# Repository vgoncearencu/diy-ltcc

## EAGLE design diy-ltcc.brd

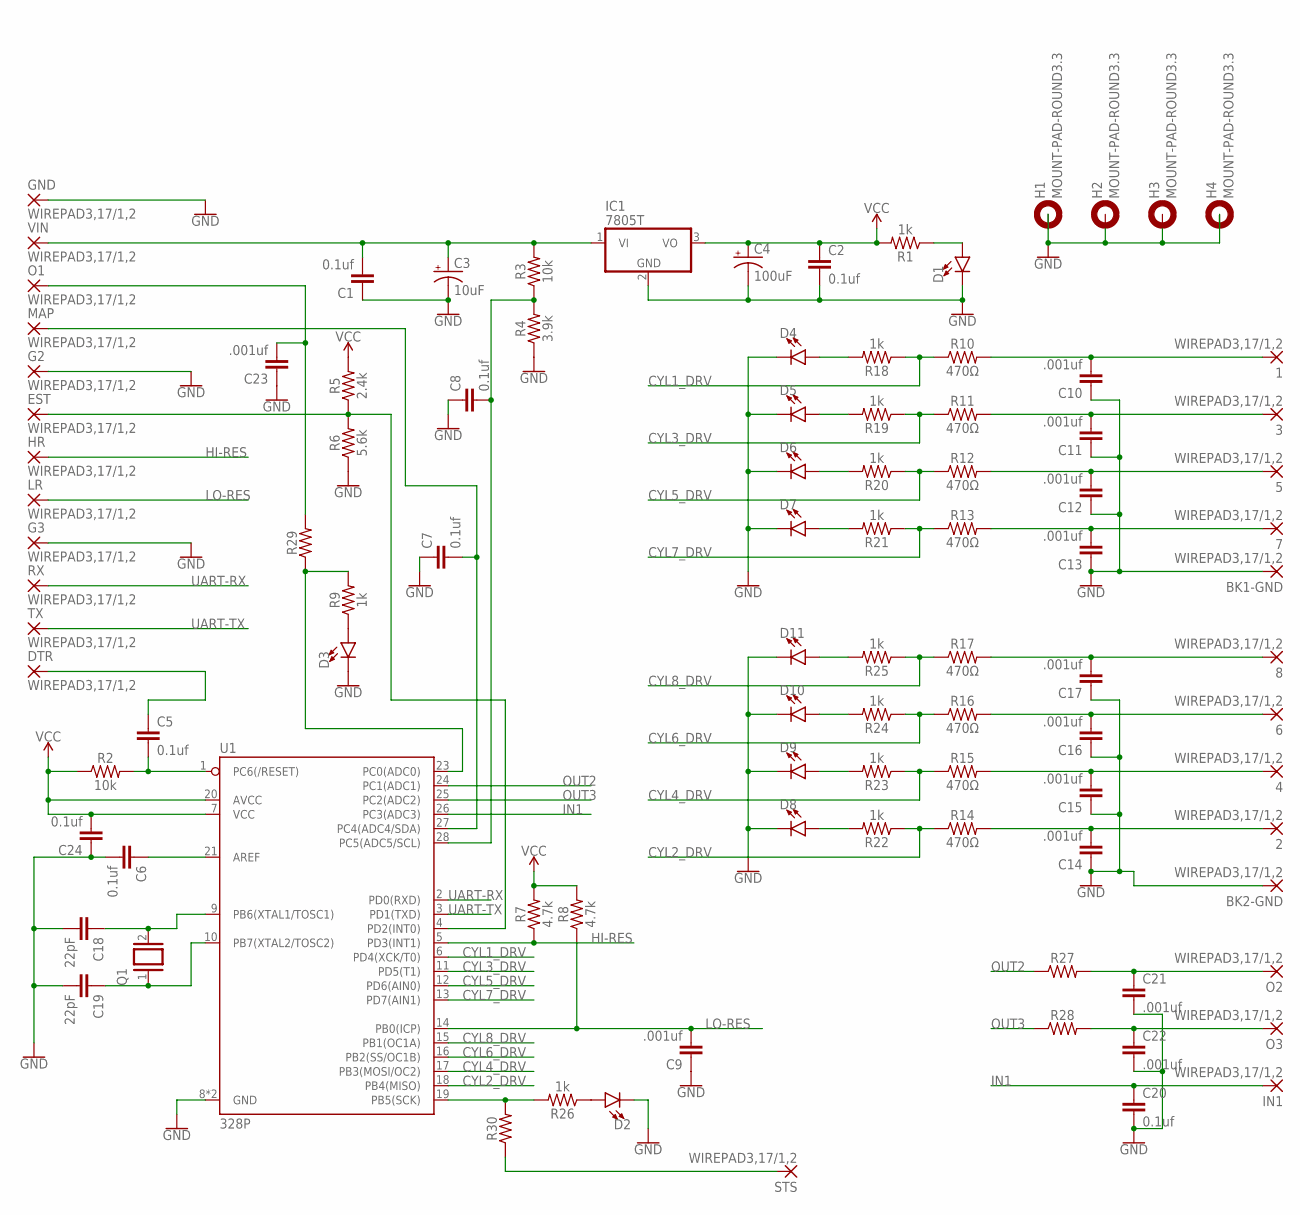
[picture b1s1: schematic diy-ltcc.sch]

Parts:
1, 2, 3, 4, 5, 6, 7, 8: WIREPAD3,17/1,2; 3,17/1,2
BK1-GND, BK2-GND: WIREPAD3,17/1,2; 3,17/1,2
C1, C2, C5, C6, C7, C8, C20, C24: 0.1uf; CAP-PTH-2.54
C3: 10uF; CPOL-RADIAL-2.5MM-5MM-KIT
C4: 100uF; CPOL-RADIAL-2.5MM-6.5MM
C9, C10, C11, C12, C13, C14, C15, C16, C17, C21, C22, C23: .001uf; CAP-PTH-2.54
C18, C19: 22pF; CAP-PTH-2.54
D1, D2, D3, D4, D5, D6, D7, D8, D9, D10, D11: LED3MM; LED_3MM
DTR: WIREPAD3,17/1,2; 3,17/1,2
EST: WIREPAD3,17/1,2; 3,17/1,2
G2, G3: WIREPAD3,17/1,2; 3,17/1,2
GND: WIREPAD3,17/1,2; 3,17/1,2
H1, H2, H3, H4: MOUNT-PAD-ROUND3.3; 3,3-PAD
HR: WIREPAD3,17/1,2; 3,17/1,2
IC1: 7805T; TO220H
IN1: WIREPAD3,17/1,2; 3,17/1,2
LR: WIREPAD3,17/1,2; 3,17/1,2
MAP: WIREPAD3,17/1,2; 3,17/1,2
O1, O2, O3: WIREPAD3,17/1,2; 3,17/1,2
Q1: XTAL/S; QS
R1, R9, R18, R19, R20, R21, R22, R23, R24, R25, R26: 1k; AXIAL-0.3
R2, R3: 10k; AXIAL-0.3
R4: 3.9k; AXIAL-0.3
R5: 2.4k; AXIAL-0.3
R6: 5.6k; AXIAL-0.3
R7, R8: 4.7k; AXIAL-0.3
R10, R11, R12, R13, R14, R15, R16, R17: 470Ω; AXIAL-0.3
R27, R28, R29, R30: 1KOHM-HORIZ-1/4W-1%; AXIAL-0.3
RX: WIREPAD3,17/1,2; 3,17/1,2
STS: WIREPAD3,17/1,2; 3,17/1,2
TX: WIREPAD3,17/1,2; 3,17/1,2
U1: 328P; DIP28
VIN: WIREPAD3,17/1,2; 3,17/1,2

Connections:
CYL1_DRV: R10.P$1 (1), R18.P$1 (1), U1.6 (PD4(XCK/T0))
CYL2_DRV: R14.P$1 (1), R22.P$1 (1), U1.18 (PB4(MISO))
CYL3_DRV: R11.P$1 (1), R19.P$1 (1), U1.11 (PD5(T1))
CYL4_DRV: R15.P$1 (1), R23.P$1 (1), U1.17 (PB3(MOSI/OC2))
CYL5_DRV: R12.P$1 (1), R20.P$1 (1), U1.12 (PD6(AIN0))
CYL6_DRV: R16.P$1 (1), R24.P$1 (1), U1.16 (PB2(SS/OC1B))
CYL7_DRV: R13.P$1 (1), R21.P$1 (1), U1.13 (PD7(AIN1))
CYL8_DRV: R17.P$1 (1), R25.P$1 (1), U1.15 (PB1(OC1A))
DTR: C5.1, DTR.1
GND: BK1-GND.1, BK2-GND.1, C1.1, C2.2, C3.2 (-), C4.2 (-), C6.2, C7.1, C8.1, C9.1, C10.1, C11.1, C12.1, C13.1, C14.1, C15.1, C16.1, C17.1, C18.2, C19.2, C20.2, C21.2, C22.2, C23.1, C24.1, D1.K (C), D2.K (C), D3.K (C), D4.K (C), D5.K (C), D6.K (C), D7.K (C), D8.K (C), D9.K (C), D10.K (C), D11.K (C), G2.1, G3.1, GND.1, H1.B3,3, H2.B3,3, H3.B3,3, H4.B3,3, IC1.2 (GND), R4.P$1 (1), R6.P$1 (1), U1.8 (GND), U1.22 (GND)
HI-RES: HR.1, R7.P$1 (1), U1.5 (PD3(INT1))
IN1: C20.1, IN1.1, U1.26 (PC3(ADC3))
LO-RES: C9.2, LR.1, R8.P$1 (1), U1.14 (PB0(ICP))
unnamed: D1.A, R1.P$1 (1)
unnamed: C5.2, R2.P$2 (2), U1.1 (PC6(/RESET))
unnamed: C6.1, U1.21 (AREF)
unnamed: C8.2, R3.P$1 (1), R4.P$2 (2), U1.28 (PC5(ADC5/SCL))
unnamed: C1.2, C3.1 (+), IC1.1 (VI), R3.P$2 (2), VIN.1
unnamed: C7.2, MAP.1, U1.27 (PC4(ADC4/SDA))
unnamed: EST.1, R5.P$1 (1), R6.P$2 (2), U1.4 (PD2(INT0))
unnamed: R9.P$2 (2), R29.P$1 (1), U1.23 (PC0(ADC0))
unnamed: D3.A, R9.P$1 (1)
unnamed: 7.1, C13.2, R13.P$2 (2)
unnamed: 5.1, C12.2, R12.P$2 (2)
unnamed: 3.1, C11.2, R11.P$2 (2)
unnamed: 1.1, C10.2, R10.P$2 (2)
unnamed: D2.A, R26.P$1 (1)
unnamed: 8.1, C17.2, R17.P$2 (2)
unnamed: 6.1, C16.2, R16.P$2 (2)
unnamed: 4.1, C15.2, R15.P$2 (2)
unnamed: 2.1, C14.2, R14.P$2 (2)
unnamed: R26.P$2 (2), R30.P$2 (2), U1.19 (PB5(SCK))
unnamed: D8.A, R22.P$2 (2)
unnamed: D9.A, R23.P$2 (2)
unnamed: D10.A, R24.P$2 (2)
unnamed: D11.A, R25.P$2 (2)
unnamed: D7.A, R21.P$2 (2)
unnamed: D6.A, R20.P$2 (2)
unnamed: D5.A, R19.P$2 (2)
unnamed: D4.A, R18.P$2 (2)
unnamed: C18.1, Q1.2, U1.9 (PB6(XTAL1/TOSC1))
unnamed: C19.1, Q1.1, U1.10 (PB7(XTAL2/TOSC2))
unnamed: C23.2, O1.1, R29.P$2 (2)
unnamed: C22.1, O3.1, R28.P$2 (2)
unnamed: C21.1, O2.1, R27.P$2 (2)
unnamed: R30.P$1 (1), STS.1
OUT2: R27.P$1 (1), U1.24 (PC1(ADC1))
OUT3: R28.P$1 (1), U1.25 (PC2(ADC2))
UART-RX: RX.1, U1.2 (PD0(RXD))
UART-TX: TX.1, U1.3 (PD1(TXD))
VCC: C2.1, C4.1 (+), C24.2, IC1.3 (VO), R1.P$2 (2), R2.P$1 (1), R5.P$2 (2), R7.P$2 (2), R8.P$2 (2), U1.7 (VCC), U1.20 (AVCC)

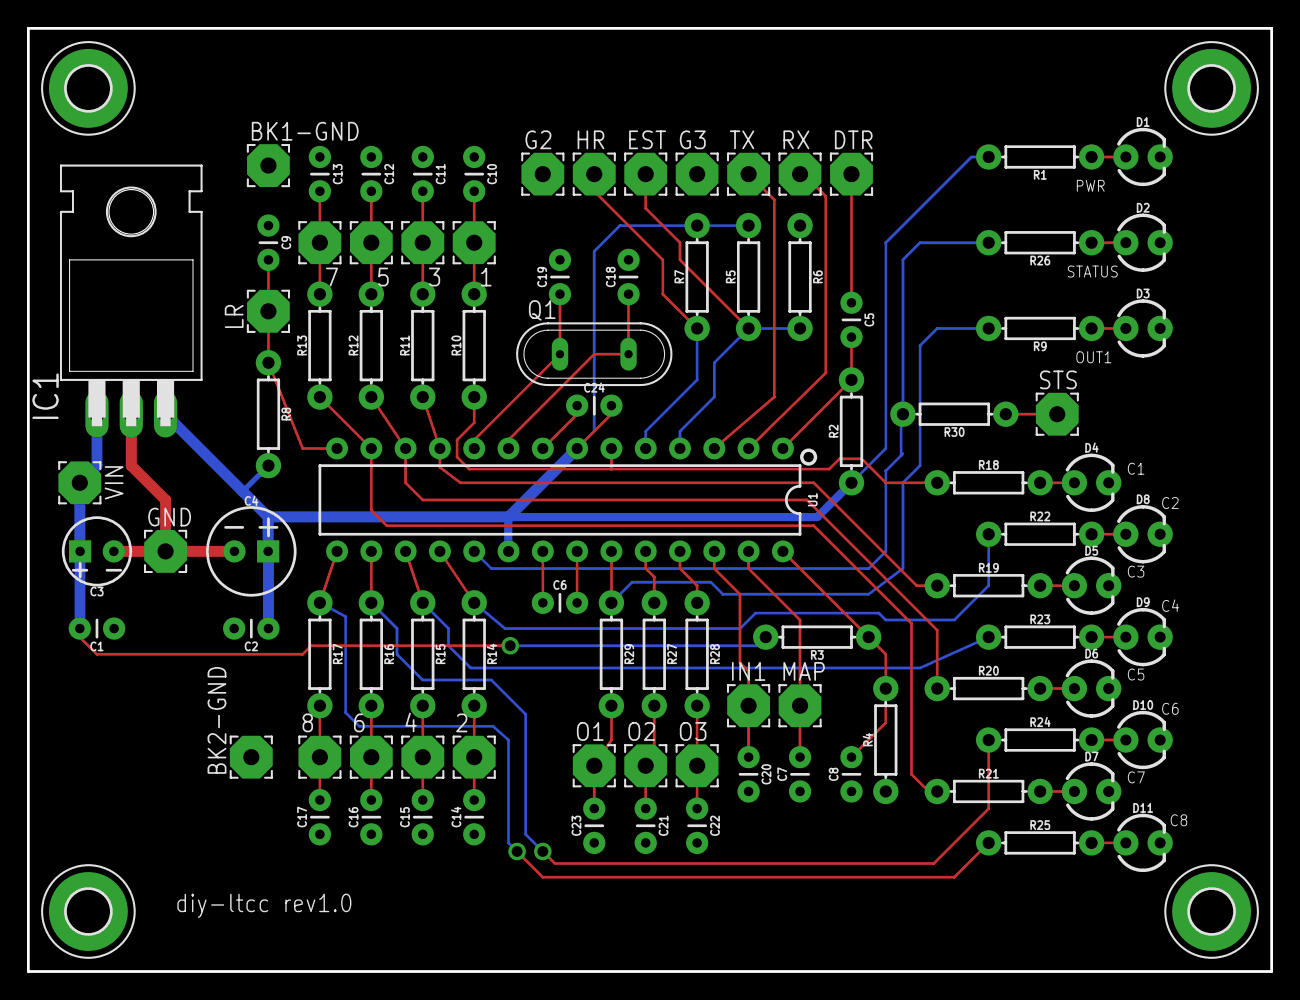
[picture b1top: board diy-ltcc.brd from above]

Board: 2 copper layers, 92.1 x 69.8 mm, 98 parts (0 on the bottom side), 51 nets.

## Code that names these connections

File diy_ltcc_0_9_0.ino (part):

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  
  
  // configure output pins
  DDRD = DDRD | B11110000; // configure PD4 - PD7 (arduino d4 - d7) as outputs
  DDRB = DDRB | B00011110; // configure PB1 - PB5 (arduino d9 - d12) as outputs
  
  Serial.begin(115200);
  Serial.print("diy-ltcc-");
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
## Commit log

2018-01-15 Initial code commit 0.9.0
2018-01-15 added disclaimer header and license notice
2018-01-17 Added ign ckt voltage detect for dwell comp
    Fully functional proof of concept.
2018-01-18 Bugfix in getDwell(), added 17v dwell row
    fixed bug in getDwell() where it would return 0 for out of range system voltages
    added 17v dwell row
    ended dwell at tdc to prevent blowing fuse if est signal lost
2018-01-24 Tables built by precompiler, move to pgm memory
    All table population handled by precompiler and stored in flash / program memory (thanks dzidav8!)
    Expanded dwellTable to 2d and increased to 16 bit
    Added accelComp table
    Changed voltage detection to calculate millivolts, rounding handled in main loop and passed to external routines as a voltage index
    Numerous other changes & code optimizations
2018-01-24 Most current tested build
    Direct copy of 0.9.7
2018-01-24 Tables built by precompiler, move to pgm memory
    All table population handled by precompiler and stored in flash / program memory (thanks dzidav8!)
    Expanded dwellTable to 2d and increased to 16 bit
    Added accelComp table
    Changed voltage detection to calculate millivolts, rounding handled in main loop and passed to external routines as a voltage index
    Numerous other changes & code optimizations
    Fix couple typos in comments
2018-01-26 Ion sense trigger, fixed timer2 prescaler
    Added ion sense trigger output on pin A1
    Fixed timer2 prescalers that were using prescaler constants for timer1
2018-05-08 Removed all floating point math and simulator mode
    Significant rewrite eliminates all floating point math during operation. Removed simulator mode. Reworked uart logging mechanism. MAP input for dwell compensation working but needs testing.
    Starts and runs reliably with no noticeable problems not attributable to other variables. Should be considered highly experimental.
2018-06-13 Initial eagle schematic and pcb layouts
2018-06-22 Final rev1 ckt and board design
    Untested final rev1 board design and schematic

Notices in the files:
diy_ltcc_0_9_0.ino:
this code is licensed under GNU General Public Licencse v3 - please see file: LICENSE in repository
parts and their libraries:
SparkFun-Capacitors: Licensing: Creative Commons ShareAlike 4.0 International - https://creativecommons.org/licenses/by-sa/4.0
